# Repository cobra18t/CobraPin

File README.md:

# CobraPin
Pinball Controller based on OPP and designed for use with MPF

Visit https://pinballmakers.com/wiki/index.php?title=CobraPin for more information

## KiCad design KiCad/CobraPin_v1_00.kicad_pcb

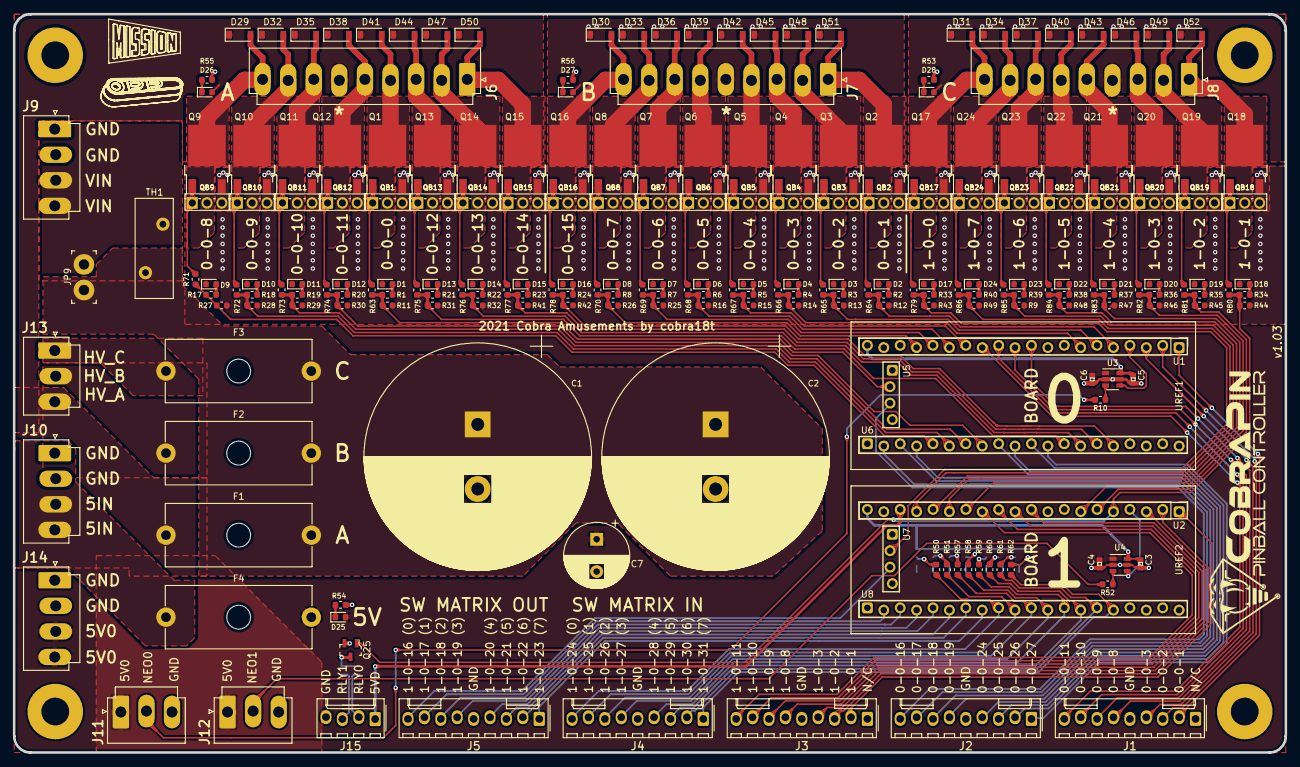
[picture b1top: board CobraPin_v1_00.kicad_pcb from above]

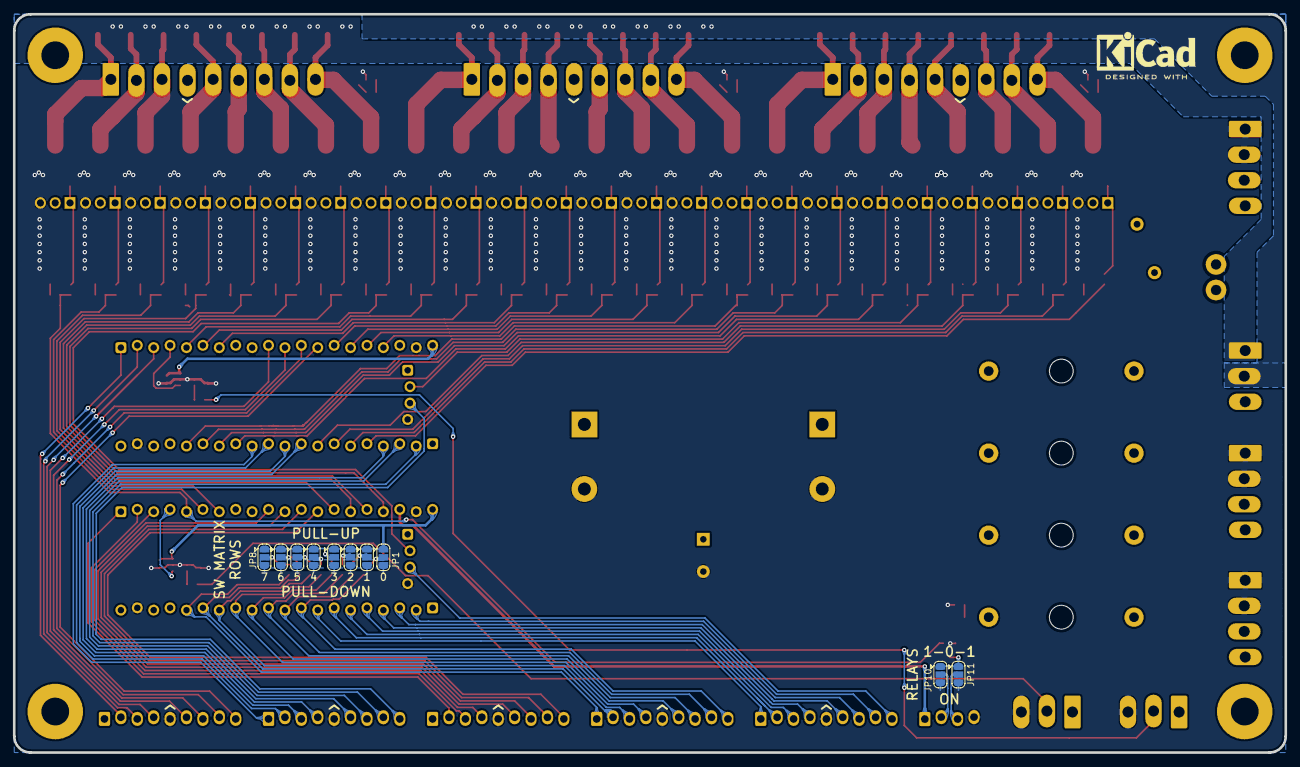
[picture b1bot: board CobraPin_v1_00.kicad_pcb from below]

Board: 2 copper layers, 196.9 x 114.3 mm, 235 parts (10 on the bottom side), 166 nets.

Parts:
C1, C2: 10,000uF; CP_Radial_D35.0mm_P10.00mm_SnapIn
C3, C4, C5, C6: 0.1uF; 0402
C7: 1000uF; CP_Radial_D10.0mm_P5.00mm
D1, D2, D3, D4, D5, D6, D7, D8, D9, D10, D11, D12, D13, D14, D15, D16, D17, D18, D19, D20, D21, D22, D23, D24: YELLOW; LED_0603_1608Metric
D25: RED; LED_0603_1608Metric
D26, D27, D28: BLUE; LED_0603_1608Metric
D29, D30, D31, D32, D33, D34, D35, D36, D37, D38, D39, D40, D41, D42, D43, D44, D45, D46, D47, D48, D49, D50, D51, D52: 1A 1000V; D_SOD-123
F1, F2, F3, F4: Fuse; Fuseholder_Cylinder-5x20mm_Schurter_0031_8201_Horizontal_Op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
J1, J2, J3, J4, J5: CONN_09; Molex_KK-254_AE-6410-09A_1x09_P2.54mm_Vertical_Lock
J6, J7, J8: CONN_09; JST_VH_B9P-VH_1x09_P3.96mm_Vertical_LongPads_Lock
J9, J10, J14: CONN_04; JST_VH_B4P-VH_1x04_P3.96mm_Vertical_LongPads_Lock
J11, J12, J13: CONN_03; JST_VH_B3P-VH_1x03_P3.96mm_Vertical_LongPads_Lock
J15: CONN_04; Molex_KK-254_AE-6410-09A_1x04_P2.54mm_Vertical_Lock
JP1, JP2, JP3, JP4, JP5, JP6, JP7, JP8, JP10, JP11: SolderJumper_3_Open; SolderJumper-3_P1.3mm_Open_RoundedPad1.0x1.5mm
JP9: Jumper; PinHeader_1x2_P3.96mm_Drill1.6mm_TEF
Q1, Q2, Q3, Q4, Q5, Q6, Q7, Q8, Q9, Q10, Q11, Q12, Q13, Q14, Q15, Q16, Q17, Q18, Q19, Q20, Q21, Q22, Q23, Q24: LSGG10R085W3; TO-252-2
Q25: 2N7002; SOT-23-3
QB1, QB2, QB3, QB4, QB5, QB6, QB7, QB8, QB9, QB10, QB11, QB12, QB13, QB14, QB15, QB16, QB17, QB18, QB19, QB20, QB21, QB22, QB23, QB24: TO251; TO-251-3_Vertical
R1, R2, R3, R4, R5, R6, R7, R8, R17, R18, R19, R20, R21, R22, R23, R24, R33, R34, R35, R36, R37, R38, R39, R40, R54: 1K; R_0603_1608Metric
R9, R11, R12, R13, R14, R15, R16, R25, R26, R27, R28, R29, R30, R31, R32, R41, R42, R43, R44, R45, R46, R47, R48, R49, R50, R51, R57, R58, R59, R60, R61, R62: 10K; R_0603_1608Metric
R10, R52: 68; R_0603_1608Metric
R53, R55, R56: 33K; R_0603_1608Metric
R63, R64, R65, R66, R67, R68, R69, R70, R71, R72, R73, R74, R75, R76, R77, R78, R79, R80, R81, R82, R83, R84, R85, R86: 100; R_0603_1608Metric
TH1: NTC 1.5ohm @ 25C; RV_Disc_D15.5mm_W5.9mm_P7.5mm_TEF
U1, U2: STM32_BluePill_ProgHeader_Separate_A; 1x20_FEMALE_LOCK
U3, U4: SN74LVC1T45DBV; SOT-23-6
U5, U7: STM32_BluePill_ProgHeader_Separate_B; 1x04_FEMALE_LOCK
U6, U8: STM32_BluePill_ProgHeader_Separate_C; 1x20_FEMALE_LOCK
UREF1, UREF2: STM32_BluePill_ProgHeader_REF

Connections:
3.3V: C5.1, U1.20, U3.6
+3V3: C3.1, JP1.1, JP2.1, JP3.1, JP4.1, JP5.1, JP6.1, JP7.1, JP8.1, U2.20, U4.6
+5V: C4.1, C6.1, C7.1, D25.2, F4.2, J11.1, J12.1, J14.3, J14.4, U3.1, U4.1
+5VD: J15.1, U2.18
/NEO_DOUT0_3V3: U1.4, U3.4
/NEO_DOUT1_3V3: U2.4, U4.4
/PWR/HV_In: J9.3, J9.4, JP9.1, TH1.2
/SOLENOID/SOLENOID_0-0: D41.2, J6.4, Q1.2, QB1.2
/SOLENOID/SOLENOID_0-1: D51.2, J7.1, Q2.2, QB2.2
/SOLENOID/SOLENOID_0-2: D48.2, J7.2, Q3.2, QB3.2
/SOLENOID/SOLENOID_0-3: D45.2, J7.3, Q4.2, QB4.2
/SOLENOID/SOLENOID_0-4: D42.2, J7.4, Q5.2, QB5.2
/SOLENOID/SOLENOID_0-5: D39.2, J7.6, Q6.2, QB6.2
/SOLENOID/SOLENOID_0-6: D36.2, J7.7, Q7.2, QB7.2
/SOLENOID/SOLENOID_0-7: D33.2, J7.8, Q8.2, QB8.2
/SOLENOID/SOLENOID_0-8: D29.2, J6.9, Q9.2, QB9.2
/SOLENOID/SOLENOID_0-9: D32.2, J6.8, Q10.2, QB10.2
/SOLENOID/SOLENOID_0-10: D35.2, J6.7, Q11.2, QB11.2
/SOLENOID/SOLENOID_0-11: D38.2, J6.5, Q12.2, QB12.2
/SOLENOID/SOLENOID_0-12: D44.2, J6.3, Q13.2, QB13.2
/SOLENOID/SOLENOID_0-13: D47.2, J6.2, Q14.2, QB14.2
/SOLENOID/SOLENOID_0-14: D50.2, J6.1, Q15.2, QB15.2
/SOLENOID/SOLENOID_0-15: D30.2, J7.9, Q16.2, QB16.2
/SOLENOID/SOLENOID_1-0: D31.2, J8.9, Q17.2, QB17.2
/SOLENOID/SOLENOID_1-1: D52.2, J8.1, Q18.2, QB18.2
/SOLENOID/SOLENOID_1-2: D49.2, J8.2, Q19.2, QB19.2
/SOLENOID/SOLENOID_1-3: D46.2, J8.3, Q20.2, QB20.2
/SOLENOID/SOLENOID_1-4: D43.2, J8.5, Q21.2, QB21.2
/SOLENOID/SOLENOID_1-5: D40.2, J8.6, Q22.2, QB22.2
/SOLENOID/SOLENOID_1-6: D37.2, J8.7, Q23.2, QB23.2
/SOLENOID/SOLENOID_1-7: D34.2, J8.8, Q24.2, QB24.2
/SOL_0-0: R1.1, R11.1, R63.1, U5.2
/SOL_0-1: R2.1, R12.1, R64.1, U1.5
/SOL_0-2: R3.1, R13.1, R65.1, U1.6
/SOL_0-3: R4.1, R14.1, R66.1, U1.7
/SOL_0-4: R5.1, R15.1, R67.1, U1.14
/SOL_0-5: R6.1, R16.1, R68.1, U1.15
/SOL_0-6: R7.1, R25.1, R69.1, U1.16
/SOL_0-7: R8.1, R26.1, R70.1, U1.17
/SOL_0-8: R17.1, R27.1, R71.1, U6.5
/SOL_0-9: R18.1, R28.1, R72.1, U6.6
/SOL_0-10: R19.1, R29.1, R73.1, U6.7
/SOL_0-11: R20.1, R30.1, R74.1, U6.8
/SOL_0-12: R21.1, R31.1, R75.1, U6.13
/SOL_0-13: R22.1, R32.1, R76.1, U6.14
/SOL_0-14: R23.1, R41.1, R77.1, U6.15
/SOL_0-15: R24.1, R42.1, R78.1, U6.16
/SOL_1-0: R33.1, R43.1, R79.1, U7.2
/SOL_1-1: Q25.1, R34.1, R44.1, R80.1, U2.5
/SOL_1-2: R35.1, R45.1, R81.1, U2.6
/SOL_1-3: R36.1, R46.1, R82.1, U2.7
/SOL_1-4: R37.1, R47.1, R83.1, U2.14
/SOL_1-5: R38.1, R48.1, R84.1, U2.15
/SOL_1-6: R9.1, R39.1, R85.1, U2.16
/SOL_1-7: R40.1, R49.1, R86.1, U2.17
/SWMATIN_0: J4.9, R50.1, U8.9
/SWMATIN_1: J4.8, R51.1, U8.10
/SWMATIN_2: J4.7, R57.1, U8.11
/SWMATIN_3: J4.6, R58.1, U8.12
/SWMATIN_4: J4.4, R59.1, U8.13
/SWMATIN_5: J4.3, R60.1, U8.14
/SWMATIN_6: J4.2, R61.1, U8.15
/SWMATIN_7: J4.1, R62.1, U8.16
/SWMATOUT_0: J5.9, U7.3
/SWMATOUT_1: J5.8, U8.2
/SWMATOUT_2: J5.7, U8.3
/SWMATOUT_3: J5.6, U8.4
/SWMATOUT_4: J5.4, U8.5
/SWMATOUT_5: J5.3, U8.6
/SWMATOUT_6: J5.2, U8.7
/SWMATOUT_7: J5.1, U8.8
/SWSOL_0-1: J1.2, U1.1
/SWSOL_0-2: J1.3, U1.2
/SWSOL_0-3: J1.4, U1.3
/SWSOL_0-8: J1.6, U1.10
/SWSOL_0-9: J1.7, U1.11
/SWSOL_0-10: J1.8, U1.12
/SWSOL_0-11: J1.9, U1.13
/SWSOL_0-16: J2.9, U5.3
/SWSOL_0-17: J2.8, U6.2
/SWSOL_0-18: J2.7, U6.3
/SWSOL_0-19: J2.6, U6.4
/SWSOL_0-24: J2.4, U6.9
/SWSOL_0-25: J2.3, U6.10
/SWSOL_0-26: J2.2, U6.11
/SWSOL_0-27: J2.1, U6.12
/SWSOL_1-1: J3.2, U2.1
/SWSOL_1-2: J3.3, U2.2
/SWSOL_1-3: J3.4, U2.3
/SWSOL_1-8: J3.6, U2.10
/SWSOL_1-9: J3.7, U2.11
/SWSOL_1-10: J3.8, U2.12
/SWSOL_1-11: J3.9, U2.13
GNDD: C1.2, C2.2, C3.2, C4.2, C5.2, C6.2, C7.2, D1.1, D2.1, D3.1, D4.1, D5.1, D6.1, D7.1, D8.1, D9.1, D10.1, D11.1, D12.1, D13.1, D14.1, D15.1, D16.1, D17.1, D18.1, D19.1, D20.1, D21.1, D22.1, D23.1, D24.1, J1.5, J2.5, J3.5, J4.5, J5.5, J9.1, J9.2, J10.1, J10.2, J11.3, J12.3, J14.1, J14.2, J15.4, JP1.3, JP2.3, JP3.3, JP4.3, JP5.3, JP6.3, JP7.3, JP8.3, JP10.3, JP11.3, Q1.3, Q2.3, Q3.3, Q4.3, Q5.3, Q6.3, Q7.3, Q8.3, Q9.3, Q10.3, Q11.3, Q12.3, Q13.3, Q14.3, Q15.3, Q16.3, Q17.3, Q18.3, Q19.3, Q20.3, Q21.3, Q22.3, Q23.3, Q24.3, Q25.2, QB1.3, QB2.3, QB3.3, QB4.3, QB5.3, QB6.3, QB7.3, QB8.3, QB9.3, QB10.3, QB11.3, QB12.3, QB13.3, QB14.3, QB15.3, QB16.3, QB17.3, QB18.3, QB19.3, QB20.3, QB21.3, QB22.3, QB23.3, QB24.3, R9.2, R11.2, R12.2, R13.2, R14.2, R15.2, R16.2, R25.2, R26.2, R27.2, R28.2, R29.2, R30.2, R31.2, R32.2, R41.2, R42.2, R43.2, R44.2, R45.2, R46.2, R47.2, R48.2, R49.2, R53.2, R54.2, R55.2, R56.2, U1.19, U2.19, U3.2, U3.5, U4.2, U4.5, U5.4, U6.19, U7.4, U8.19
unnamed: C1.1, C2.1, F1.2, F2.2, F3.2, JP9.2, TH1.1
unnamed: D1.2, R1.2
unnamed: D2.2, R2.2
unnamed: D3.2, R3.2
unnamed: D4.2, R4.2
unnamed: D5.2, R5.2
unnamed: D6.2, R6.2
unnamed: D7.2, R7.2
unnamed: D8.2, R8.2
unnamed: D9.2, R17.2
unnamed: D10.2, R18.2
unnamed: D11.2, R19.2
unnamed: D12.2, R20.2
unnamed: D13.2, R21.2
unnamed: D14.2, R22.2
unnamed: D15.2, R23.2
unnamed: D16.2, R24.2
unnamed: D17.2, R33.2
unnamed: D18.2, R34.2
unnamed: D19.2, R35.2
unnamed: D20.2, R36.2
unnamed: D21.2, R37.2
unnamed: D22.2, R38.2
unnamed: D23.2, R39.2
unnamed: D24.2, R40.2
unnamed: D25.1, R54.1
unnamed: D26.1, R55.1
unnamed: D27.1, R56.1
unnamed: D28.1, R53.1
unnamed: F4.1, J10.3, J10.4
unnamed: J11.2, R10.1
unnamed: J12.2, R52.1
unnamed: J15.2, JP10.2
unnamed: J15.3, JP11.2
unnamed: JP1.2, R50.2
unnamed: JP2.2, R51.2
unnamed: JP3.2, R57.2
unnamed: JP4.2, R58.2
unnamed: JP5.2, R59.2
unnamed: JP6.2, R60.2
unnamed: JP7.2, R61.2
unnamed: JP8.2, R62.2
unnamed: JP10.1, JP11.1, Q25.3
unnamed: Q1.1, QB1.1, R63.2
unnamed: Q2.1, QB2.1, R64.2
unnamed: Q3.1, QB3.1, R65.2
unnamed: Q4.1, QB4.1, R66.2
unnamed: Q5.1, QB5.1, R67.2
unnamed: Q6.1, QB6.1, R68.2
unnamed: Q7.1, QB7.1, R69.2
unnamed: Q8.1, QB8.1, R70.2
unnamed: Q9.1, QB9.1, R71.2
unnamed: Q10.1, QB10.1, R72.2
unnamed: Q11.1, QB11.1, R73.2
unnamed: Q12.1, QB12.1, R74.2
unnamed: Q13.1, QB13.1, R75.2
unnamed: Q14.1, QB14.1, R76.2
unnamed: Q15.1, QB15.1, R77.2
unnamed: Q16.1, QB16.1, R78.2
unnamed: Q17.1, QB17.1, R79.2
unnamed: Q18.1, QB18.1, R80.2
unnamed: Q19.1, QB19.1, R81.2
unnamed: Q20.1, QB20.1, R82.2
unnamed: Q21.1, QB21.1, R83.2
unnamed: Q22.1, QB22.1, R84.2
unnamed: Q23.1, QB23.1, R85.2
unnamed: Q24.1, QB24.1, R86.2
unnamed: R10.2, U3.3
unnamed: R52.2, U4.3
VbankA: D26.2, D29.1, D32.1, D35.1, D38.1, D41.1, D44.1, D47.1, D50.1, F1.1, J6.6, J13.3
VbankB: D27.2, D30.1, D33.1, D36.1, D39.1, D42.1, D45.1, D48.1, D51.1, F2.1, J7.5, J13.2
VbankC: D28.2, D31.1, D34.1, D37.1, D40.1, D43.1, D46.1, D49.1, D52.1, F3.1, J8.4, J13.1

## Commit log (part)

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2021-01-16 added initial OPP config files
2021-01-16 Create CobraPin_Standard_NoGlow_1
2021-01-16 Rename CobraPin_Standard_0.py to OPP config/CobraPin_Standard_0.py
2021-01-16 Create CobraPin_Standard_NoGlow_0
2021-04-15 Update CobraPin_Standard_NoGlow_1
2021-04-15 Rename CobraPin_Standard_NoGlow_0 to CobraPin_Standard_NoGlow_0.py
2021-04-15 Rename CobraPin_Standard_NoGlow_1 to CobraPin_Standard_NoGlow.py_1
2021-04-15 Rename CobraPin_Standard_NoGlow.py_1 to CobraPin_Standard_NoGlow_1.py
2021-04-15 Rename CobraPin_Standard_NoGlow_0.py to CobraPin_Board0_NoGlow.py
2021-04-15 Rename CobraPin_Standard_0.py to CobraPin_Board0.py
2021-04-15 Rename CobraPin_Direct_1.py to CobraPin_Board1_Direct.py
2021-04-15 Rename CobraPin_HighMatrix_1.py to CobraPin_Board1_HighMatrix.py
2021-04-15 Rename CobraPin_Standard_1.py to CobraPin_Board1_Standard.py
2021-04-15 Rename CobraPin_Standard_NoGlow_1.py to CobraPin_Board1_Standard_NoGlow.py
2021-08-28 Create license
2021-08-28 Add KiCad source files
2021-09-27 Adding example of lamp matrix config
2021-09-27 Added note showing that this is specific to the Xpansion board
2021-11-15 14-segment NeoSeg test game
2022-01-21 add pdf schematic
2022-08-06 Add dimensioned drawings for 8 and 2 digit
2022-10-22 Create Example Games
2022-10-22 Create sdf
2022-10-22 Create ExampleGames
2022-10-22 Create asd
2022-11-17 Adding version 2.01 CobraPin source
2022-12-20 Add workaround for OPP autofire bug
2023-01-31 add fadecandy alternative config
2023-07-27 add revised Tag Team game
2024-04-04 Add logo images
2024-08-30 Add satellite board dimension pdf
2024-09-20 Add STM32 pin mapping
2024-09-20 Add Xpansion schematic
2024-11-23 Add Board0 config with servos on 0-0-10 and 0-0-11
2025-04-22 Add config for Satellite with servos enabled
2025-06-26 Added Board 1 Direct, Servos, No glow
2025-06-28 Add Xpansion board source
2026-05-30 Add MiniProto files
2026-06-26 Add option for standard board 0 with servo on 11
